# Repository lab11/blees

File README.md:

BLEES
=====

BLEES: Bluetooth Low Energy Environment Sensors.
<br /><br />
BLEES is a 1 inch round sensor tag for sensing the ambient environment. It monitors
temperature, humidity, light, pressure, and movement and reports its readings
over BLE.
<br /><br /><br />

Hardware
--------
The BLEES hardware is a small, once inch round sensor board that mounts onto a [Squall](https://github.com/helena-project/squall) BLE sensor tag. The board 
currently has four sensors:

1. Temperature and Humidity (Si7021)
2. Pressure (LPS331AP)
3. Light (TSL2561)
4. Accelerometer (ADXL362)

The BLEES hardware is located in the `hardware` directory, where you can find
the Eagle design files.

Software
--------
The [Squall](https://github.com/helena-project/squall) uses the software
located in the `software` directory. Follow the directions in the [nrf5x-base Readme]
(http://github.com/lab11/nrf5x-base#program-a-nrf51822) to
get your machine set up to build and flash the Squall.

The primary application is
[`software/apps/blees`](https://github.com/lab11/blees/tree/master/software/apps/blees).
This application samples the
sensors and makes this data available as both broadcast advertisements and the
Environmental Sensing Service for a connected device.

Data Reference
--------------
### Advertisement data
BLEES transmits advertisements every 1000 ms containing application data.
[Here's a useful BLE Advertisement
primer](http://www.argenox.com/bluetooth-low-energy-ble-v4-0-development/library/a-ble-advertising-primer/).
The advertisements come in two forms: environmental data and eddystone.
Advertisements alternate between the two evenly.

The environmental data advertised is same data as is available through the
environmental sensing service, but broadcast so several nearby devices can
access it concurrently. The data includes, in order, four bytes for pressure,
two bytes for humidity, two bytes for temperature, two bytes for light
illuminance, and one byte for acceleration state. An example application that
collects BLE advertisements from BLEES devices and displays the data can be
found at `data_collection/advertisements/blees_adv.js`

[Eddystone](https://github.com/google/eddystone) is a protocol for connecting
BLE devices to Internet resources. BLEES advertises the URL of an application
that can be interpreted by the Summon framework in order to automatically
generate a user interface. (see next heading)

### Environmental Sensing Service
BLEES is also connectable and supports the Environmental Sensing Service. While
connected to, it continues to advertise, but only one connection at a time is
allowed. The environmental sensing service is defined by the
[BLE SIG](https://www.bluetooth.org/en-us/specification/assigned-numbers/environmental-sensing-service-characteristics).

Summon App
----------
[Summon](https://github.com/lab11/summon) is a UI application for BLE devices.
Rather than requiring every user
to install a new app for every BLE device, Summon allows BLE devices to
point to their own HTML/JS based interface and loads it in a single
application. BLEES supports the summon architecture and provides
a Summon application.

Cloning
-------
To clone both this repository and the required submodules,
clone with the `--recursive` option: 
`git clone --recursive git@github.com:lab11/blees.git`

Otherwise, you can initialize the submodule and keep submodules up to
date by doing `git submodule update --init --recursive`

If you think all of this is ridiculous and git should just handle submodules automatically, use this:
https://gist.github.com/brghena/fc4483a2df83c47660a5

Other Hardware
--------------

Included in this repo are:

### Blink

Blink is a PIR sensor that is also based on Squall. Like BLEES, it supports Summon.
The nRF51822 app is [here](https://github.com/lab11/blees/tree/master/software/apps/blink).

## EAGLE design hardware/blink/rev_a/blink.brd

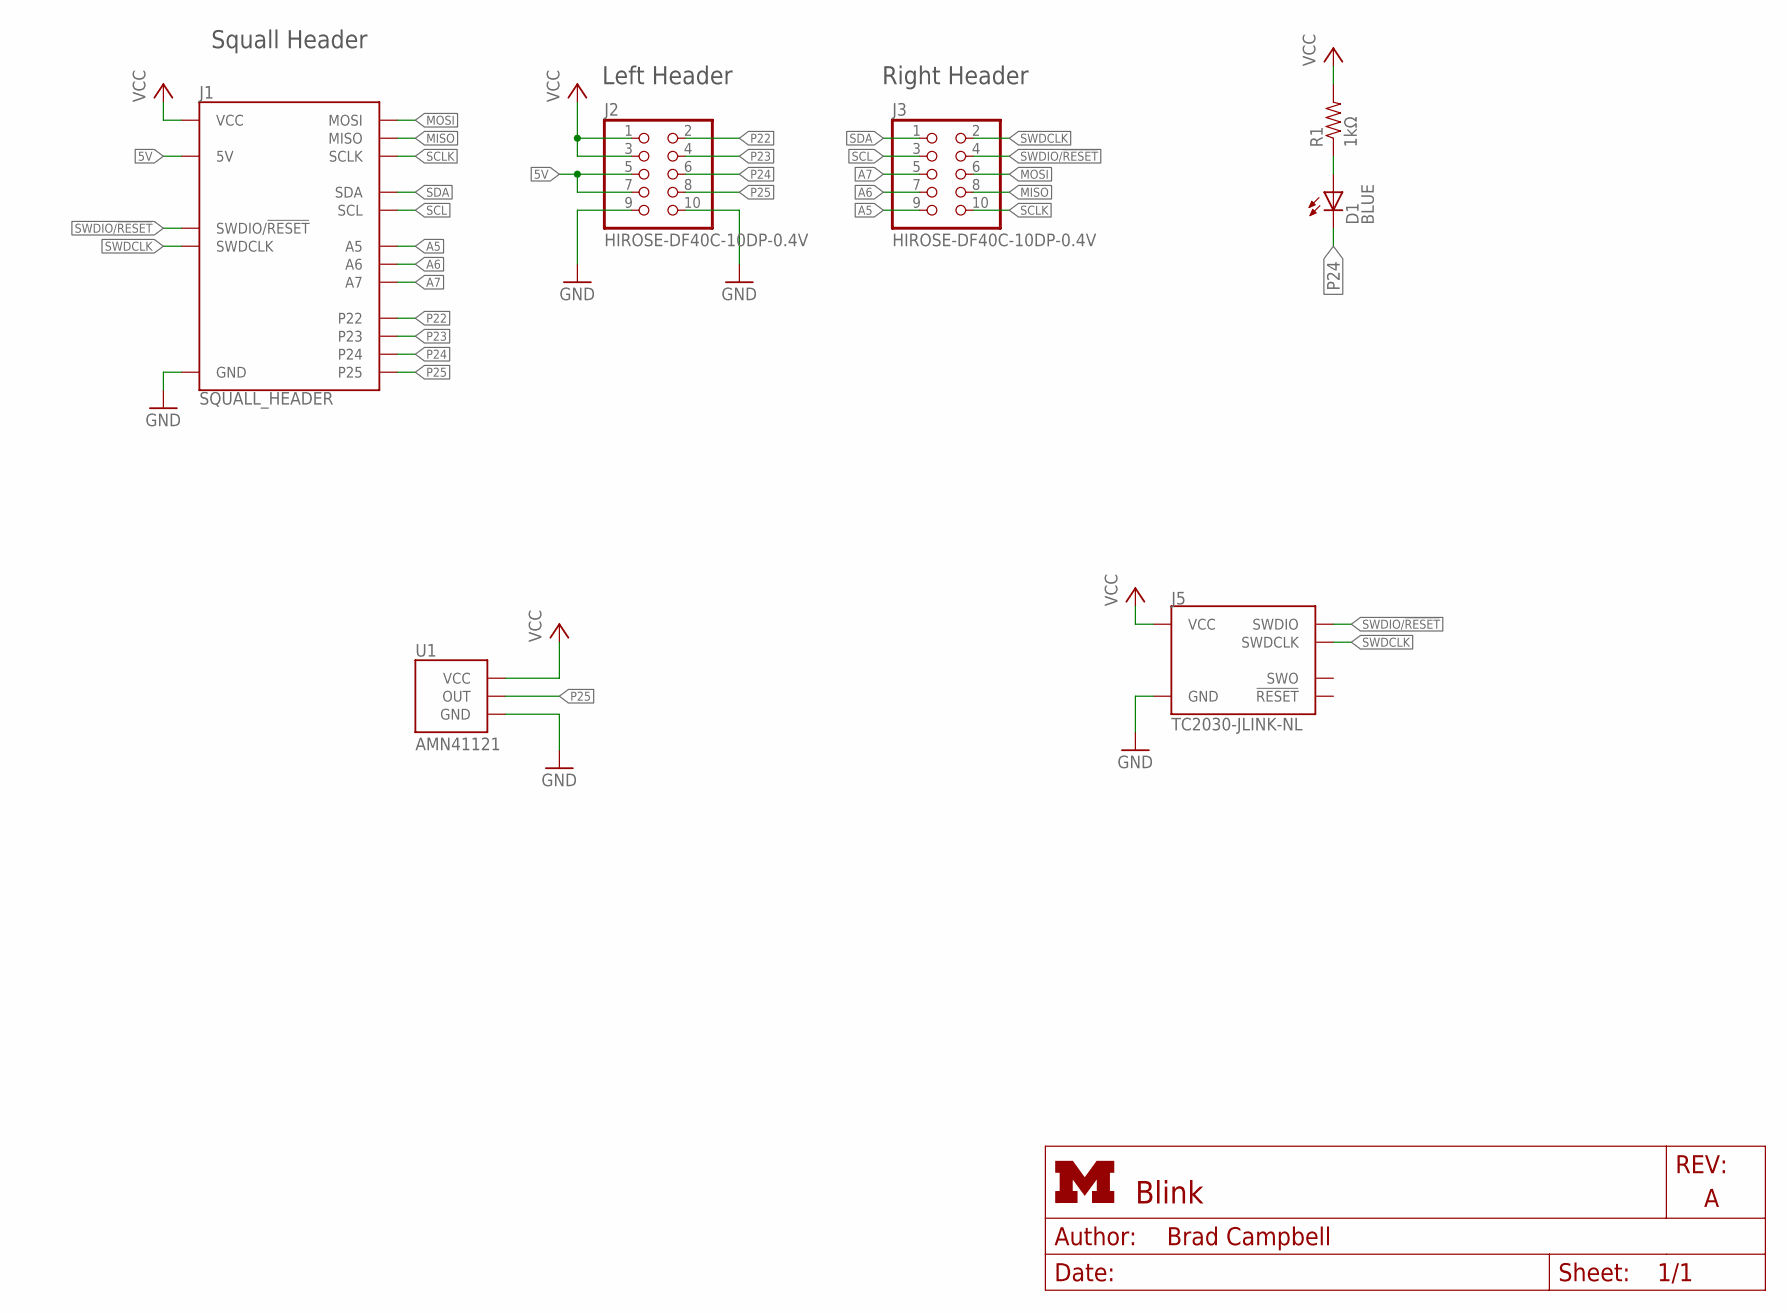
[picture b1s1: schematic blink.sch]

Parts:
D1: BLUE; LED-0603
J1: SQUALL_HEADER
J2, J3: HIROSE-DF40C-10DP-0.4V; 2X5/SMD/0.4MM
J5: TC2030-JLINK-NL; TC2030-IDC-NL
R1: 1kΩ; 0402_RES
U1: AMN41121; AMN2; DIGIKEY 255-3065-ND

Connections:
5V: J1.A5 (5V), J1.A7 (5V), J2.5, J2.7
A5: J1.B9 (A5), J3.9
A6: J1.B7 (A6), J3.7
A7: J1.B5 (A7), J3.5
GND: J1.A9 (GND), J1.A10 (GND), J2.9, J2.10, J5.5 (GND), U1.GND
MISO: J1.B8 (MISO), J3.8
MOSI: J1.B6 (MOSI), J3.6
unnamed: D1.A, R1.1
P22: J1.A2 (P22), J2.2
P23: J1.A4 (P23), J2.4
P24: D1.C, J1.A6 (P24), J2.6
P25: J1.A8 (P25), J2.8, U1.OUT
SCL: J1.B3 (SCL), J3.3
SCLK: J1.B10 (SCLK), J3.10
SDA: J1.B1 (SDA), J3.1
SWDCLK: J1.B2 (SWDCLK), J3.2, J5.4 (SWDCLK)
SWDIO/!RESET: J1.B4 (SWDIO/!RESET), J3.4, J5.2 (SWDIO)
VCC: J1.A1 (VCC), J1.A3 (VCC), J2.1, J2.3, J5.1 (VCC), R1.2, U1.VCC

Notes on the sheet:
Squall Header
Left Header
Right Header

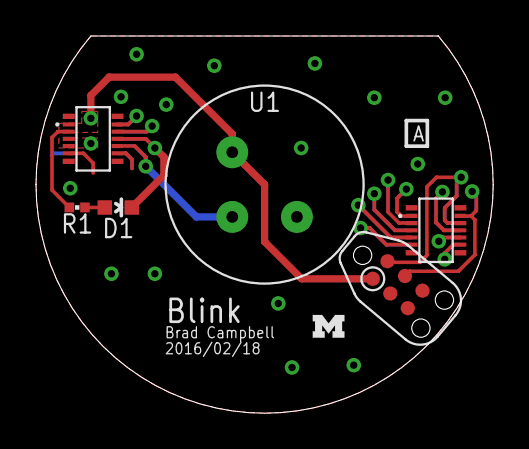
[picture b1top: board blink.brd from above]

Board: 2 copper layers, 25.4 x 21.0 mm, 8 parts (0 on the bottom side), 18 nets.

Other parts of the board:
U$1: UMICH_SOLID_50MIL

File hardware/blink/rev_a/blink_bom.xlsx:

Qty | Value | Device | Package | Parts | Description | DIGIKEY | MOUSER | NEWARK
DNP | BLUE | LED0603 | LED-0603 | D1 | LEDs
2 | SQUALL_HEADER | SQUALL_HEADER | SQUALL_HEADER | J1 | Header for a sensor board on top of the Squall BLE tag board. | H11617CT-ND
DNP | HIROSE-DF40C-10DP-0.4V | HIROSE-DF40C-10DP-0.4V | 2X5/SMD/0.4MM | J2, J3 | DF40 Series Header - 0.4MM Pitch | H11616CT-ND | 798-DF40C10DP0.4V51 | 68X2585
DNP | 1kΩ | RESISTOR0402_RES | 0402_RES | R1 | Resistor
1 | AMN41121 | AMN41121 | AMN2 | U1 | Passive infrared human detection sensor with built-in amp. | 255-2651-ND

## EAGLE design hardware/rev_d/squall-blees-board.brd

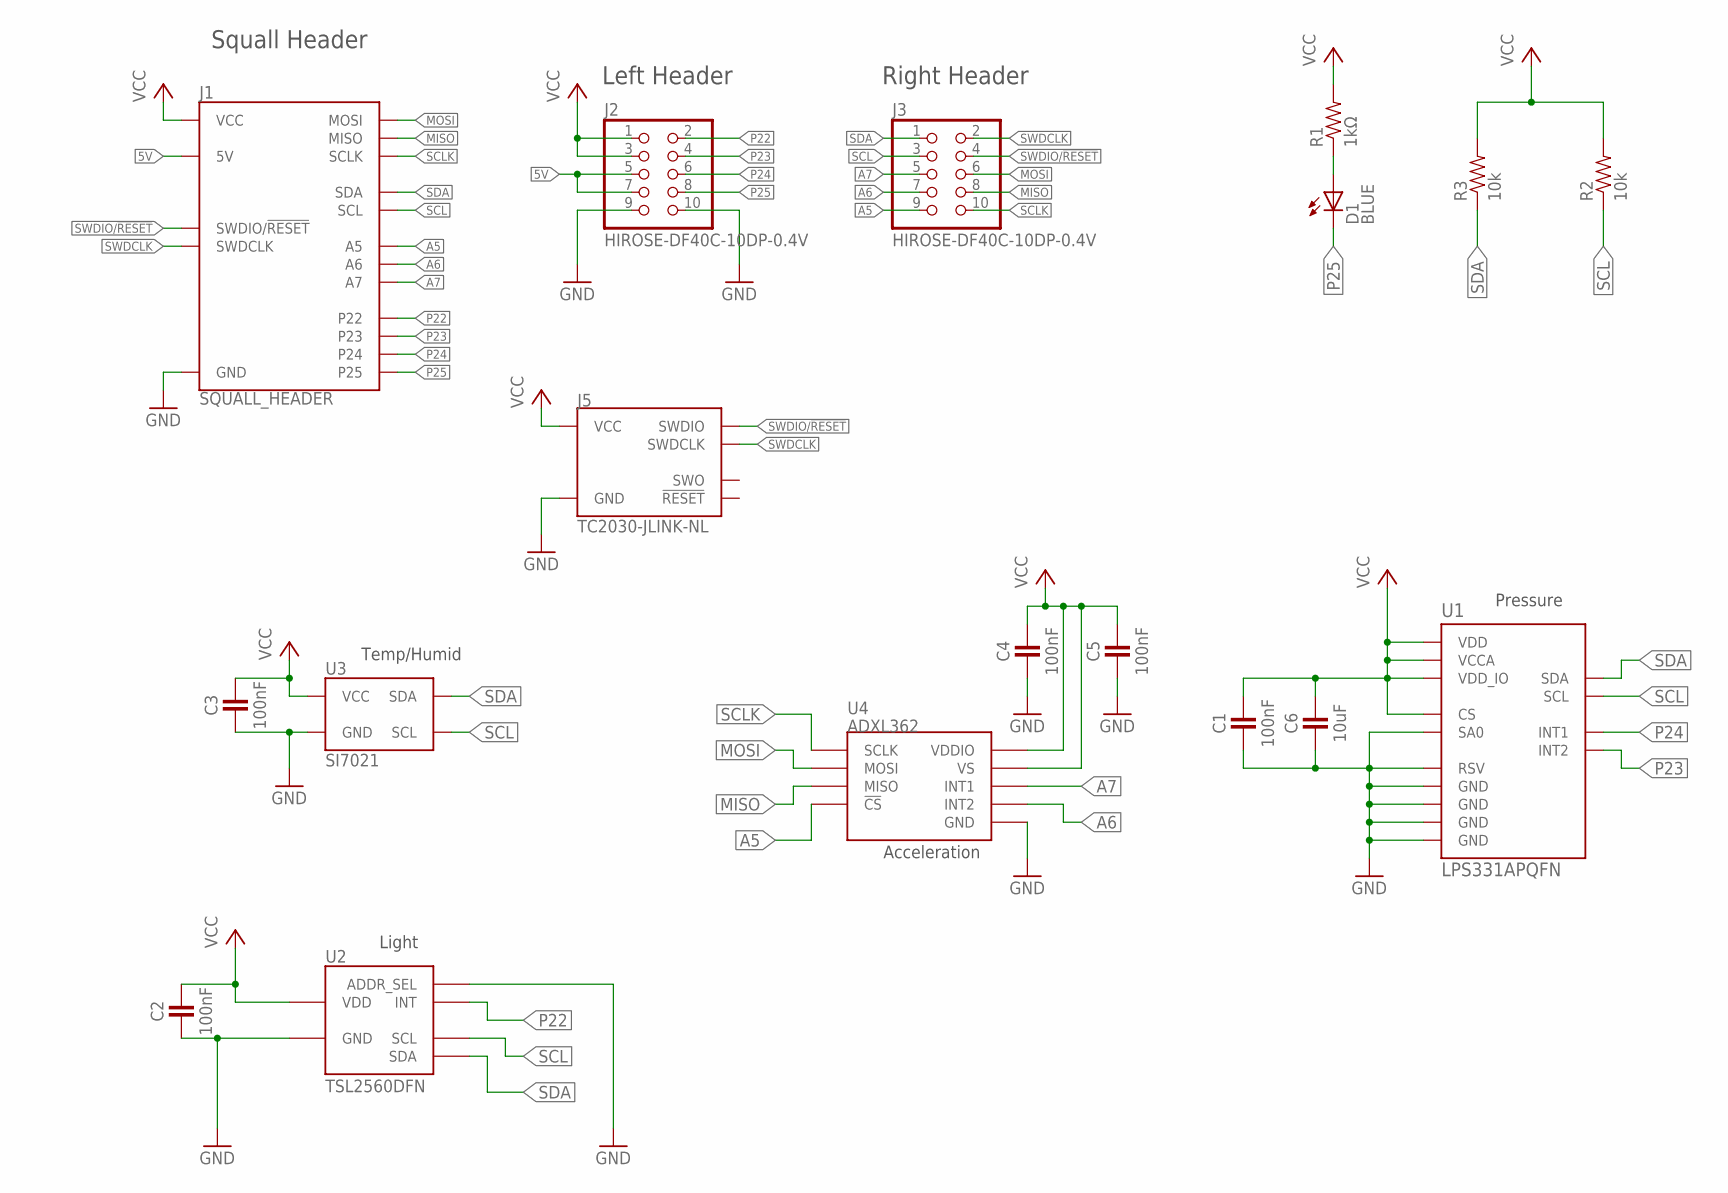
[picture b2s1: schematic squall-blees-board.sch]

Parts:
C1, C2, C3, C4, C5: 100nF; 0402_CAP
C6: 10uF; 0603_CAP
D1: BLUE; LED-0603
J1: SQUALL_HEADER
J2, J3: HIROSE-DF40C-10DP-0.4V; 2X5/SMD/0.4MM
J5: TC2030-JLINK-NL; TC2030-IDC-NL
R1: 1kΩ; 0402_RES
R2, R3: 10k; 0402_RES
U1: LPS331APQFN; HCLGA-16L
U2: TSL2560DFN; DFN2
U3: SI7021; DFN-6/3MM
U4: ADXL362

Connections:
5V: J1.A5 (5V), J1.A7 (5V), J2.5, J2.7
A5: J1.B9 (A5), J3.9, U4.P$8 (!CS)
A6: J1.B7 (A6), J3.7, U4.P$9 (INT2)
A7: J1.B5 (A7), J3.5, U4.P$11 (INT1)
GND: C1.2, C2.2, C3.2, C4.2, C5.2, C6.2, J1.A9 (GND), J1.A10 (GND), J2.9, J2.10, J5.5 (GND), U1.5 (GND), U1.7 (SA0), U1.10 (RSV), U1.12 (GND), U1.13 (GND), U1.16 (GND), U2.2 (ADDR_SEL), U2.3 (GND), U3.2 (GND), U4.P$12 (GND), U4.P$13 (GND), U4.P$16 (GND)
MISO: J1.B8 (MISO), J3.8, U4.P$7 (MISO)
MOSI: J1.B6 (MOSI), J3.6, U4.P$6 (MOSI)
unnamed: D1.A, R1.1
P22: J1.A2 (P22), J2.2, U2.5 (INT)
P23: J1.A4 (P23), J2.4, U1.9 (INT2)
P24: J1.A6 (P24), J2.6, U1.11 (INT1)
P25: D1.C, J1.A8 (P25), J2.8
SCL: J1.B3 (SCL), J3.3, R2.1, U1.4 (SCL), U2.4 (SCL), U3.6 (SCL)
SCLK: J1.B10 (SCLK), J3.10, U4.P$4 (SCLK)
SDA: J1.B1 (SDA), J3.1, R3.1, U1.6 (SDA), U2.6 (SDA), U3.1 (SDA)
SWDCLK: J1.B2 (SWDCLK), J3.2, J5.4 (SWDCLK)
SWDIO/!RESET: J1.B4 (SWDIO/!RESET), J3.4, J5.2 (SWDIO)
VCC: C1.1, C2.1, C3.1, C4.1, C5.1, C6.1, J1.A1 (VCC), J1.A3 (VCC), J2.1, J2.3, J5.1 (VCC), R1.2, R2.2, R3.2, U1.1 (VDD_IO), U1.8 (CS), U1.14 (VDD), U1.15 (VCCA), U2.1 (VDD), U3.5 (VCC), U4.P$1 (VDDIO), U4.P$14 (VS)

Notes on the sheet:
Squall Header
Left Header
Right Header
Pressure
Acceleration
Light
Temp/Humid

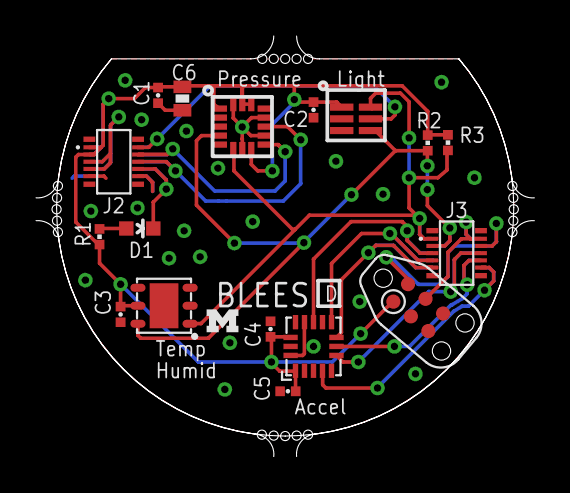
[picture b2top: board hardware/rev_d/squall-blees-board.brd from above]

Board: 2 copper layers, 27.7 x 23.4 mm, 19 parts (0 on the bottom side), 18 nets.

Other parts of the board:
U$1: UMICH_SOLID_50MIL

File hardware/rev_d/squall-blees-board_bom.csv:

Qty,Value,Device,Package,Parts,Description,DIGIKEY,MOUSER,NEWARK
5,100nF,CAPACITOR,0402_CAP,"C1, C2, C3, C4, C5",0402 Capacitor,1276-1442-6-ND,,
1,10uF,CAPACITOR0603_CAP,0603_CAP,C6,0603 Capacitor,1276-1119-6-ND,,
1,BLUE,LED0603,LED-0603,D1,LEDs,160-1647-1-ND,,
2,SQUALL_HEADER,SQUALL_HEADER,SQUALL_HEADER,J1,Header for a sensor board on top of the Squall BLE tag board.,H11617CT-ND,,
2,HIROSE-DF40C-10DP-0.4V,HIROSE-DF40C-10DP-0.4V,2X5/SMD/0.4MM,"J2, J3",DF40 Series Header - 0.4MM Pitch,H11616CT-ND,798-DF40C10DP0.4V51,68X2585
1,1k,RESISTOR0402_RES,0402_RES,R1,0402 Resistor,RHM1.0KCECT-ND,,
2,10k,RESISTOR0402_RES,0402_RES,"R2, R3",0402 Resistor,RHM10.0KCDCT-ND,,
1,LPS331APQFN,LPS331APQFN,HCLGA-16L,U1,LPS331AP pressure sensor,,,52X6707
1,TSL2561DFN,TSL2561DFN,DFN2,U2,TSL2561 light to digital converter,TSL2561-FNDKR-ND,,
1,Si7021,Si7021,DFN,U3,Si7021 temperature/humidity sensor,336-2542-1-ND,,
1,ADXL362,ADXL362,ADXL362,U4,Micropower 3-axis accelerometer,ADXL362BCCZ-R2DKR-ND,,

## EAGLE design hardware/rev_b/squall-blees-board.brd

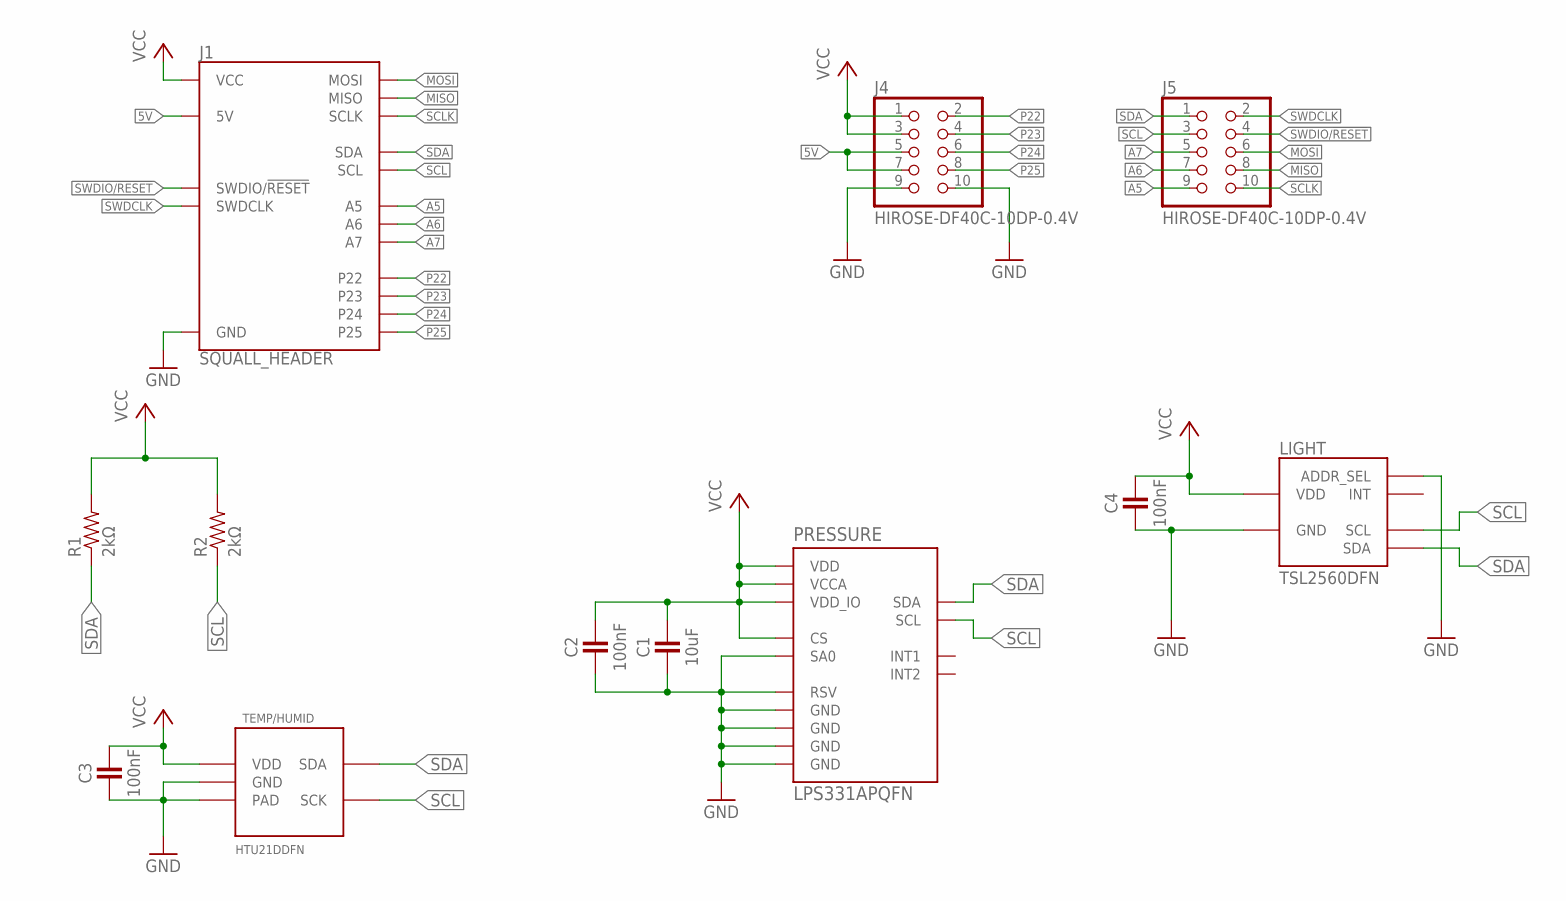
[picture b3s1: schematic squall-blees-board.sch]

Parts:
C1: 10uF; 0603_CAP
C2, C3, C4: 100nF; 0402_CAP
J1: SQUALL_HEADER
J4, J5: HIROSE-DF40C-10DP-0.4V; 2X5/SMD/0.4MM
LIGHT: TSL2560DFN; DFN2
PRESSURE: LPS331APQFN; HCLGA-16L
R1, R2: 2kΩ; 0402_RES
TEMP/HUMID: HTU21DDFN; DFN

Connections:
5V: J1.A5 (5V), J1.A7 (5V), J4.5, J4.7
A5: J1.B9 (A5), J5.9
A6: J1.B7 (A6), J5.7
A7: J1.B5 (A7), J5.5
GND: C1.2, C2.2, C3.2, C4.2, J1.A9 (GND), J1.A10 (GND), J4.9, J4.10, LIGHT.2 (ADDR_SEL), LIGHT.3 (GND), PRESSURE.5 (GND), PRESSURE.7 (SA0), PRESSURE.10 (RSV), PRESSURE.12 (GND), PRESSURE.13 (GND), PRESSURE.16 (GND), TEMP/HUMID.5 (GND), TEMP/HUMID.PAD
MISO: J1.B8 (MISO), J5.8
MOSI: J1.B6 (MOSI), J5.6
P22: J1.A2 (P22), J4.2
P23: J1.A4 (P23), J4.4
P24: J1.A6 (P24), J4.6
P25: J1.A8 (P25), J4.8
SCL: J1.B3 (SCL), J5.3, LIGHT.4 (SCL), PRESSURE.4 (SCL), R2.1, TEMP/HUMID.1 (SCK)
SCLK: J1.B10 (SCLK), J5.10
SDA: J1.B1 (SDA), J5.1, LIGHT.6 (SDA), PRESSURE.6 (SDA), R1.1, TEMP/HUMID.6 (SDA)
SWDCLK: J1.B2 (SWDCLK), J5.2
SWDIO/!RESET: J1.B4 (SWDIO/!RESET), J5.4
VCC: C1.1, C2.1, C3.1, C4.1, J1.A1 (VCC), J1.A3 (VCC), J4.1, J4.3, LIGHT.1 (VDD), PRESSURE.1 (VDD_IO), PRESSURE.8 (CS), PRESSURE.14 (VDD), PRESSURE.15 (VCCA), R1.2, R2.2, TEMP/HUMID.2 (VDD)

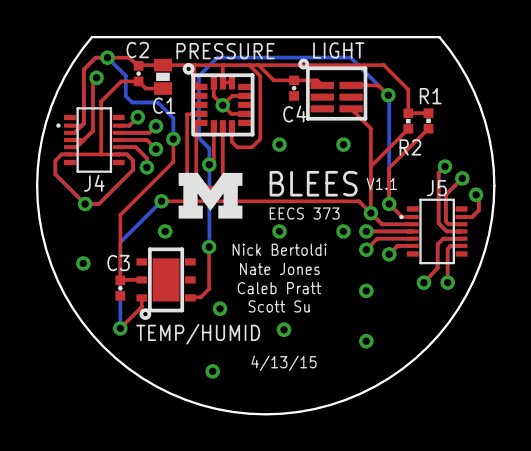
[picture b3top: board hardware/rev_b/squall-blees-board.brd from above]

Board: 2 copper layers, 25.4 x 21.0 mm, 12 parts (0 on the bottom side), 17 nets.

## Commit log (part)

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2015-03-11 Add gitignore file
2015-03-11 Add empty Android project
2015-03-16 Added base software that broadcasts bluetooth stuff
2015-03-16 Add bluetooth permissions to Android app
2015-03-17 Update Squall
2015-03-17 Remove commented out code, add options menu
2015-03-17 Add EAGLE layout base for hardware
2015-03-19 Change name and add dummy temp, humidity, and light data
2015-03-19 Add bluetooth stuff, not done yet
2015-03-23 Work on Androiid project still need to work on BLE stuff
2015-03-23 Remove debugging logs
2015-03-26 Maybe fix issue for crashing on tablets, invalidate view rather than reset the adapter
2015-03-26 Start working on communicating with sensors
2015-03-26 Use notifyDataSetChanged, which is what we should be using
2015-03-26 Make debug versions have different names so they don't conflict with release versions
2015-03-27 Ignore settings file, and generated EAGLE files
2015-03-27 comment out I2C stuff
2015-03-27 Move Makefile to template since user needs to customize
2015-03-27 Added update function for broadcast info
2015-03-27 Added timer interrupts
2015-03-27 Read from [x] Pressure; [ ] Temp/Hum; [ ] Lux
2015-03-27 Better refresh capabilities
2015-03-27 Incriment version num
2015-03-31 All sensors now communicating. Light sensor is very funky though, and only sometimes works. Note that the light sensor is only working due to a hack and the fact that the TWI library seems to be bugg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
2015-04-01 Add a couple components we use, and add Lab11s components that we will use
2015-04-02 Work on circuit board
2015-04-03 Board finished
2015-04-03 Add PDF, font is very small for some reason, will look into why later
2015-04-05 Some work done on using floats for numbers instead of 8-bit numbers. It works, but decimal places need work, and code needs cleaning
2015-04-06 Make changes to text, output gerbers, panelize
2015-04-07 New panelized boards
2015-04-07 Fix drill output, need to export with EXCELLON_24 for one reason or another
2015-04-07 Remove borders from panelized boards, and move panelized outlines to different layers in the original board. Use CAM processor to get the different outlines
2015-04-07 update version num
2015-04-09 Send sensor data as floats
2015-04-09 Use floats
2015-04-11 Add setting to upload data to server
2015-04-14 Add Rev B to fix temperature/humidity sensor connections
2015-04-14 Update rev_b, send it for fabrication
2015-04-17 4 sig digits for pressure
2015-04-19 Fix bug with multiple BLEES devices
2015-04-19 Power saving added
2015-04-19 Turns off sensors that don't need to be always on
2015-04-19 Add farenheit celcius selection (no I cannot spell)
2015-06-04 updated BLEES app
    - only uses advertisements (not scan req/resp)
    - Added sniff.js to view packets
    - set address with c0:98:e5 prefix
2015-06-09 First pass at rev C BLEES
    Includes a MPU-9250 9DOF as well as connected interrupt lines
2015-06-12 Second pass at Rev C of BLEES. Added accelerometer
2015-06-12 Panelized version of rev C BLEES
2015-06-13 Swapped out temp/humidity sensor
    This one is lower power, same functionality, and purchasable
2015-06-19 Main works with LED and populated sensors
2015-06-20 Gitignore to remove build files
2015-07-12 SPI successfully functions
2015-07-12 Revisions to BOM for assembler
2015-07-15 Update README.md with useful info
    Add some information to the README to make it easier for someone unfamiliar with the project to understand exactly what BLEES is, how the repository is laid out, and what they need in order to work o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
2015-07-22 Pressure sensor displays data
2015-07-22 Added solder paste gerber files
2015-07-23 Moved folder structure around
2015-07-23 Added nrf5x-base for software libraries
2015-07-28 Working on sensor drivers...
2015-07-29 Blink works using the nrf5x base project
2015-07-29 Moved sniffer
2015-07-29 Added basic blink application
2015-07-30 Beacons data!
2015-07-30 Fixed pressure sensor to work w/ sdk9 and updated gitignore
2015-07-31 Fixed for new SDK, accelerator data kinda working
2015-07-31 Trying to make light sensor interrupt work
2015-08-04 Interrupts work, Modes work, working on FIFO
2015-08-05 Added physical web beacon
2015-08-05 Acc interrupts working, working on light sensor one shot
2015-08-06 Got one shot mode working
2015-08-10 Almost working!
2015-08-10 Connection + Beaconing?
2015-08-10 working
2015-08-12 committing these..
2015-08-12 Continuous advertisements of correct data, can connect for temp, pres, hum
2015-08-12 Added lux characteristic
2015-08-12 Working almost
2015-08-12 Advertises while connected
2015-08-17 Acc interrupt working!!!!
2015-08-18 Working!
2015-08-18 Clean up files a bit
2015-08-18 Working?
2015-08-18 Fixed minor timing issue Working??
2015-08-19 Made acc detection better
2015-08-19 Fixed compiling issue
2015-08-19 Can config acceleration activity/inactivity from phone
2015-08-21 Added info on git submodules
2015-08-24 Somewhat better...
2015-08-24 Icons for acceleration, humidity, pressure
2015-08-25 Kind of better
2015-08-26 Parsed Advertising, Connection ability
2015-08-26 Semi working
2015-08-26 Working on descriptor writes
2015-08-26 Changed led interval, can write more to pressure
2015-08-27 Fixed connection error. Needed to close device
2015-08-27 Updated to use SDK and Softdevice in nrf5x-base
2015-08-27 Playing with new characteristic
2015-08-28 Basic working version?
2015-08-28 Not working
2015-08-28 Trying to update url to work with summon..
2015-08-28 Trying to get app to work with summon..
2015-09-16 Now works with size optimizations
2015-09-16 Updating app. Doesn't interpret url as data
2015-09-16 Testing if commits work
2015-09-16 Editing format...
2015-09-17 Work in progress...
2015-09-17 Advertisements never stop
2015-09-18 Well then...
2015-09-20 Updated to use new simple_ble and eddystone libs
2015-09-20 Got rid of extraneous header includes
2015-09-20 Modified to use callback for app errors
2015-09-21 file format to unix EVERYWHERE
2015-09-21 Update to newest commit
2015-09-30 Power consumption much better now. 582.67uW
2015-09-30 Updated to new version of nrf5x-base
2015-09-30 Updated nrf5x-base. Also, typo
2015-10-07 couple more changes to app, icon
2015-10-07 More sensitive to acc & led back
2015-10-07 added image
2015-10-07 add pic to readme
2015-10-07 little update on readme
2015-10-08 Option to set device BLE address at flash time
2015-10-08 And the Flash Address location
2015-10-08 add stuff for blees sign
2015-10-08 transparent background
2015-10-08 Convert for brad
2015-10-08 added advertisement for blees
2015-10-08 Made lux interval larger :(
2015-10-11 move summon apps to their own folder
2015-10-11 update blees poster with urls
2015-10-11 removing old code and modules that won't work
    the android app and node script are both out of date. and they probably
    won't be updated, so let's just remove them to not confuse the issue.
2015-10-11 name the blees app "blees"
2015-10-11 move sensor drivers to central folder
2015-10-11 add summon folder readme, rename app
    don't need -summon in the new folder
2015-10-11 update blees app readme
2015-11-09 added app for littled test
2015-11-09 add little d as submodule
2015-11-11 working on adding db to blees app
    not working, insert command isn't finishing. softdevice throwing
    assert. not sure why.
2015-11-12 got db code to at least not hard fault
2015-11-16 Updated readme with explanation of data structure
    Also included example Nodejs to parse advertisements
2015-11-30 Additional instructions
2016-01-06 change content security for images
2016-01-06 add parse file for gateway
2016-01-08 Massively reduced power needs of BLEES
    Steady state of ~1 mA changes to ~6 uA
    GPIOTE interrupts have been changed to Port interrupts rather than
    specific pin interrupts. TWI is disabled while waiting for Light sensor
    to wake up.
2016-01-08 Removed app scheduler stuff that isn't in use
2016-01-10 code cleanup
2016-01-11 update parse to match
2016-01-11 try checking again
2016-01-11 update blees to new adv format
2016-01-11 trying new adv parse in blees summon
2016-01-11 untyped languages :(
2016-01-11 testing adv parse
2016-01-11 more debg
2016-01-11 make it array buffer
2016-01-11 apparently length isnt a thing
    in this AWFUL corner of javascript
2016-01-11 oops
2016-01-11 have to read the minimal documentation
2016-01-11 try try again
2016-01-11 try this
2016-01-11 changed var name
2016-01-11 cleanup
2016-01-11 get rid of some strange code
2016-01-11 only get four packets for some reason
2016-01-11 summon app works, remove old code
2016-01-11 Updated scan script to new packet format
2016-01-13 add initial logo
2016-01-29 tried to fix signed problem in blees temperature
2016-01-29 actually fixed negative temperatures
2016-01-31 update nrf5x-base
2016-01-31 update to hopefully working parse.js for pir
2016-02-04 update to light sensor driver
    trying to fix invalid values
2016-02-04 Moving to SDK10. It builds!
2016-02-04 Moving BLEES to simple_ble. (Not tested)
2016-02-04 enable gpiote interrupts
2016-02-04 add service uuid to blees
    clean up comments
2016-02-04 deleted unused variables
2016-02-04 Update to BLEES script
    Also pulled nrf5x
2016-02-04 Update nrf5x to allow scan resp in a connection
2016-02-05 Make movement LED visible
2016-02-07 add id and hide LED
2016-02-08 addes squall pir app
2016-02-08 changed the app name
2016-02-08 tried changing back to the old format
2016-02-08 removed parse.js that wasn't squall
2016-02-09 Added BLEES current trace
2016-02-10 put my parse.js back
    JOSHKLJHSHSHSHSHSHSHS!!!!
2016-02-14 starting to build pir summon app
2016-02-14 added log for the advertisement
2016-02-14 readded the 'hack'
2016-02-14 tried to update screen with movement
2016-02-14 added a guard to protect against non-data packets
2016-02-14 trying to differentiate advertisements
2016-02-14 took away last second because it wasn't relevant
    also changed some wording
2016-02-14 added back in debugging mandata
2016-02-14 changed favicon
2016-02-20 blink
    pir board for squall
2016-02-20 moved label
2016-02-20 delete old ble apps
    either no longer needed or moved to nrf5x base
2016-02-21 Make BLEES Summon app work on iOS and Android
2016-02-21 Summon app with ios and android support
2016-02-24 add blink hardware files
2016-02-25 Properly check if manufacturerData exists
2016-03-03 add flag for pir led
2016-03-05 better image
2016-03-05 add link to readme
2016-03-05 don't need all of the node instructions
2016-03-05 add note about blink
2016-03-05 add blink updated zip
2016-03-05 update parse.js to new name
2016-03-05 update blink app readme
2016-03-11 add bom
2016-03-13 BLEES Rev D
    Added Pogo-Pin programmer
2016-03-24 Testing summon app
2016-03-24 More debug output
2016-03-24 Handle cordova loading errors
2016-03-24 Fix loading error in Summon app
2016-04-14 added support to reset accelerometer, added reset prepare for dfu
2016-04-18 Enable dc-dc converter
2016-04-18 Enable DFU on Blink
2016-04-22 update nrf5x base
2016-04-22 enable dfu for blink
    add dc dc line
2016-04-22 Update BLEES to enable wireless DFU
2016-05-13 remove enabling dcdc converter, adjust accel
    - less sensitive accelerometer
2016-05-13 no evil dc-dc
2016-05-19 Update BLEES app
    Add a sequence number to end of data
    Acceleration data has "currently active" and "in last
    minute modes"
2016-05-19 Update to include blees app changes
    Change name of acceleration indications
    Include sequence number
2016-05-19 Need to specify ram/flash settings for DFU
2016-06-07 add first attempt at blink case
2016-06-19 Update parse.js to match index.js neg temp code
2016-07-11 Moving to j2x.us
2016-07-12 Moved to j2x
2016-07-14 add blink pictures
2016-07-17 Solar BLEES!
    Reads humidity and temperature a sends their data in an advertisement,
    all while harvesting from a solar monjolo
    Still a work in progress
2016-07-21 added some changes to the readme
2016-07-22 Cleanup solar blees code
    Add timestamp to blees data collection script
2016-07-26 Added startup delay for sensor
2016-12-05 Make BOM github compliant
2017-02-01 updated PIR sensor part number
2017-06-11 changed app to have service and tried web bluetooth
2017-06-11 included javascript file
    it at least pop us the list of devices, but I can't test at home
2017-06-11 added logging function
2017-06-11 working javascript to periodically read a service

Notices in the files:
parts and their libraries:
SparkFun-LED: Licensing: CC v3.0 Share-Alike You are welcome to use this library for commercial purposes.
